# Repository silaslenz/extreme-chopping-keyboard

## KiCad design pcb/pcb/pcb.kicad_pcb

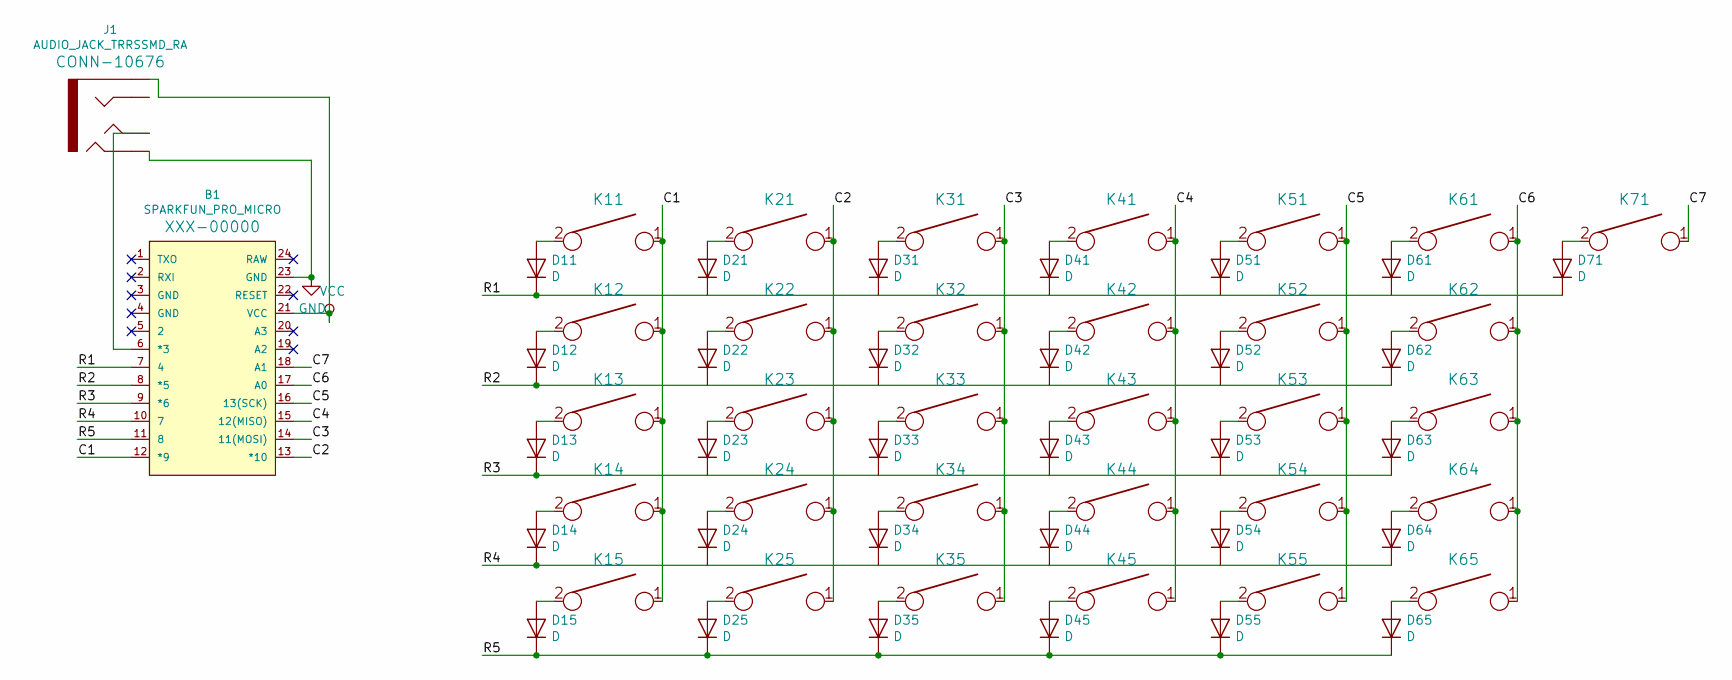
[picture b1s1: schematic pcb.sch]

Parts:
B1: SPARKFUN_PRO_MICRO
D11, D12, D13, D14, D15, D21, D22, D23, D24, D25, D31, D32, D33, D34, D35, D41, D42, D43, D44, D45, D51, D52, D53, D54, D55, D61, D62, D63, D64, D65, D71: D; D_A-405_P7.62mm_Horizontal
J1: AUDIO_JACK_TRRSSMD_RA; AUDIO_JACK_3.5MM_TRRS_SMD_RA
K11, K21, K22, K23, K24, K31, K32, K33, K34, K41, K42, K43, K44, K51, K52, K53, K54, K61, K62, K63, K64, K71: KEYSW; Mx_Alps_100
K12: KEYSW; Mx_Alps_150
K13, K65: KEYSW; Mx_Alps_175
K14, K15, K25, K35, K45, K55: KEYSW; Mx_Alps_125

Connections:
/C1: B1.12 (*9), K11.1, K12.1, K13.1, K14.1, K15.1
/C2: B1.13 (*10), K21.1, K22.1, K23.1, K24.1, K25.1
/C3: B1.14 (11(MOSI)), K31.1, K32.1, K33.1, K34.1, K35.1
/C4: B1.15 (12(MISO)), K41.1, K42.1, K43.1, K44.1, K45.1
/C5: B1.16 (13(SCK)), K51.1, K52.1, K53.1, K54.1, K55.1
/C6: B1.17 (A0), K61.1, K62.1, K63.1, K64.1, K65.1
/C7: B1.18 (A1), K71.1
/R1: B1.7 (4), D11.1 (K), D21.1 (K), D31.1 (K), D41.1 (K), D51.1 (K), D61.1 (K), D71.1 (K)
/R2: B1.8 (*5), D12.1 (K), D22.1 (K), D32.1 (K), D42.1 (K), D52.1 (K), D62.1 (K)
/R3: B1.9 (*6), D13.1 (K), D23.1 (K), D33.1 (K), D43.1 (K), D53.1 (K), D63.1 (K)
/R4: B1.10 (7), D14.1 (K), D24.1 (K), D34.1 (K), D44.1 (K), D54.1 (K), D64.1 (K)
/R5: B1.11 (8), D15.1 (K), D25.1 (K), D35.1 (K), D45.1 (K), D55.1 (K), D65.1 (K)
GND: B1.23 (GND), J1.RING (RING1)
unnamed: B1.6 (*3), J1.TIP
unnamed: D11.2 (A), K11.2
unnamed: D12.2 (A), K12.2
unnamed: D13.2 (A), K13.2
unnamed: D14.2 (A), K14.2
unnamed: D15.2 (A), K15.2
unnamed: D21.2 (A), K21.2
unnamed: D22.2 (A), K22.2
unnamed: D23.2 (A), K23.2
unnamed: D24.2 (A), K24.2
unnamed: D25.2 (A), K25.2
unnamed: D31.2 (A), K31.2
unnamed: D32.2 (A), K32.2
unnamed: D33.2 (A), K33.2
unnamed: D34.2 (A), K34.2
unnamed: D35.2 (A), K35.2
unnamed: D41.2 (A), K41.2
unnamed: D42.2 (A), K42.2
unnamed: D43.2 (A), K43.2
unnamed: D44.2 (A), K44.2
unnamed: D45.2 (A), K45.2
unnamed: D51.2 (A), K51.2
unnamed: D52.2 (A), K52.2
unnamed: D53.2 (A), K53.2
unnamed: D54.2 (A), K54.2
unnamed: D55.2 (A), K55.2
unnamed: D61.2 (A), K61.2
unnamed: D62.2 (A), K62.2
unnamed: D63.2 (A), K63.2
unnamed: D64.2 (A), K64.2
unnamed: D65.2 (A), K65.2
unnamed: D71.2 (A), K71.2
VCC: B1.21 (VCC), J1.EART (EARTH)

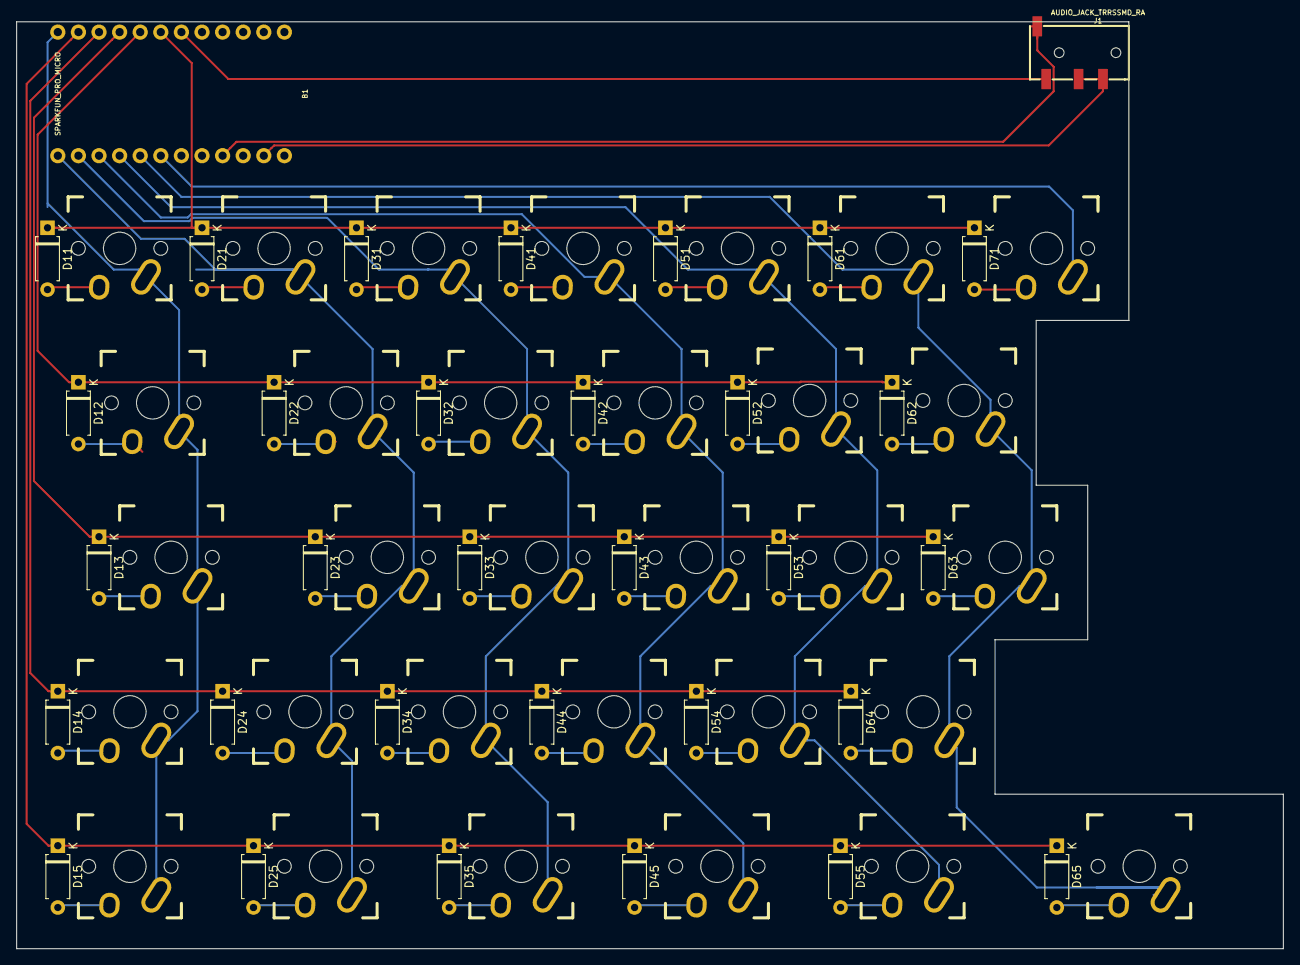
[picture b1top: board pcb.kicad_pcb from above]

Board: 2 copper layers, 156.2 x 114.3 mm, 64 parts (0 on the bottom side), 46 nets.
